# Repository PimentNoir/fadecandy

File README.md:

Fadecandy is a project that makes LED art easier, tastier, and more creative. We're all about creating tools that remove the technical drudgery from making LED art, freeing you to do more interesting, nuanced, and creative things. We think LEDs are more than just trendy display devices, we think of them as programmable light for interactive art.

* [Video Introduction to Fadecandy](https://vimeo.com/79935649)
* [Introduction by Nick Poole from Spark Fun Electronics](https://www.youtube.com/watch?v=-4AUBjV7Y-w)
* [Tutorial: LED Art with Fadecandy](https://learn.adafruit.com/led-art-with-fadecandy)
* [Tutorial: 1,500 NeoPixel LED Curtain with Raspberry Pi and Fadecandy](https://learn.adafruit.com/1500-neopixel-led-curtain-with-raspberry-pi-fadecandy/)
* [Presentation slides: Easier and Tastier LED Art with Fadecandy](http://www.misc.name/easier-and-tastier-led-art-with-fadecandy/)
* [LED Interaction Research with Fadecandy at Stimulant labs](http://stimulant.com/led-interaction-research/)

Buy a Fadecandy Controller board:

* [Adafruit](http://www.adafruit.com/products/1689)
* [RGB-123](http://rgb-123.com/product/fadecandy/)

Simple Example
--------------

Here's a simple project, a single LED strip controlled by a Processing sketch running on your laptop:

```
// Simple Processing sketch for controlling a 64-LED strip.
// A glowing color-blob appears on the strip under mouse control.

OPC opc;
PImage dot;

void setup()
{
  size(800, 200);

  // Load a sample image
  dot = loadImage("color-dot.png");

  // Connect to the local instance of fcserver
  opc = new OPC(this, "127.0.0.1", 7890);

  // Map one 64-LED strip to the center of the window
  opc.ledStrip(0, 64, width/2, height/2, width / 70.0, 0, false);
}

void draw()
{
  background(0);

  // Draw the image, centered at the mouse location
  float dotSize = width * 0.2;
  image(dot, mouseX - dotSize/2, mouseY - dotSize/2, dotSize, dotSize);
}
```

A More Complex Example
----------------------

Fadecandy is also useful for larger projects with many thousands of LEDs, and it's useful for art that runs on embedded computers like the Raspberry Pi:

Project Scope
-------------

This project is a collection of reusable pieces you can take or leave. The overall goal of making LED art easier, tastier, and more creative is a broad one. To keep this project manageable to start with, there are some rough limitations on what's supported:

* LED strips, grids, and other modules based on the WS2811 or WS2812 chip.
  * Common and inexpensive, available from [many suppliers](http://www.aliexpress.com/item/5M-WS2811-LED-digital-strip-60leds-m-with-60pcs-WS2811-built-in-tthe-5050-smd-rgb/635563383.html?tracelog=back_to_detail_a) for around $0.25 per pixel.
* Something with a USB host port that can run your art.
  * Laptops and Mac Minis work great
  * The Raspberry Pi is also a great platform for this, but it requires more technical skill
* Distances of no more than 60ft or so between your computer and your farthest LEDs
  * USB cables < 50ft
  * WS2811 data cables < 10ft
* No more than about 10000 LED pixels total
  * There's no hard limit, but it gets more difficult after this point.
* Experimental support for APA102/APA102C/SK9822 via SPI
  * Currently only works on Raspberry Pi and requires the WiringPi library. Compile with FCSERVER_HAS_WIRINGPI defined to enable support.

These are fuzzy limitations based on current software capabilities and rough electrical limits, so you may be able to stretch them. But this gives you an idea about the kind of art we try to support. Projects are generally larger than wearables, but smaller than entire buildings.

For example, the first project to use Fadecandy was the [Ardent Mobile Cloud Platform](http://scanlime.org/2013/09/the-ardent-mobile-cloud-platform/) at Burning Man 2013. This project used one Raspberry Pi, five Fadecandy controller boards, and 2500 LEDs.

Fadecandy makes no assumptions about how you generate control patterns for the LEDs. You can generate a 2D video and sample pixels from the video, you can make a 3D model of your sculpture and sample a 3D *shader* for your pixel values, or you can create a unique system specifically for your art.

Fadecandy Controller
--------------------

The centerpiece of the Fadecandy project is a controller board which can drive up to 512 LEDs (as 8 strings of 64) over USB. Many Fadecandy boards can be attached to the same computer using a USB hub or a chain of hubs.

Fadecandy makes it easy to drive these LEDs from anything with USB, and it includes unique algorithms which eliminate many of the common visual glitches you see when using these LEDs.

The LED drive engine is based on Stoffregen's excellent [OctoWS2811](http://www.pjrc.com/teensy/td_libs_OctoWS2811.html) library, which pumps out serial data for these LED strips entirely using DMA. This firmware builds on Paul's work by adding:

* A high performance USB protocol
* Zero copy architecture with triple-buffering
* Interpolation between keyframes
* Gamma and color correction with per-channel lookup tables
* Temporal dithering
* A custom PCB with line drivers and a 5V boost converter
* A fully open source bootloader

These features add up to give *very smooth* fades and high dynamic range. Ever notice that annoying stair-stepping effect when fading LEDs from off to dim? Fadecandy avoids that using a form of [delta-sigma modulation](http://en.wikipedia.org/wiki/Delta-sigma_modulation). It rapidly wiggles each pixel's value up or down by one 8-bit step, in order to achieve 16-bit resolution for fades.

Vitals
------

* 512 pixels supported per Teensy board (8 strings, 64 pixels per string)
* Very high hardware frame rate (~400 FPS) to support temporal dithering
* Full-speed (12 Mbps) USB
* 257x3-entry 16-bit color lookup table, for gamma correction and color balance

Platform
--------

Fadecandy uses the Freescale MK20DX128 microcontroller, the same one used by the [Teensy 3.0](http://www.pjrc.com/store/teensy3.html) board. Fadecandy includes its own PCB design featuring a robust power supply and level shifters. It also includes an open source bootloader compatible with the USB Device Firmware Update spec.

You can use Fadecandy either as a full hardware platform or as firmware for the Teensy 3.0 board.

Color Processing
----------------

Fadecandy internally represents colors with 16 bits of precision per channel, or 48 bits per pixel. Why 48-bit color? In combination with our dithering algorithm, this gives a lot more color resolution. It's especially helpful near the low end of the brightness range, where stair-stepping and color *popping* artifacts can be most apparent.

Each pixel goes through the following processing steps in Fadecandy:

* 8 bit per channel framebuffer values are expanded to 16 bits per channel
* We interpolate smoothly from the old framebuffer values to the new framebuffer values
* This interpolated 16-bit value goes through the color LUT, which itself is linearly interpolated
* The final 16-bit value is fed into our temporal dithering algorithm, which results in an 8-bit color
* These 8-bit colors are converted to the format needed by OctoWS2811's DMA engine
* In hardware, the converted colors are streamed out to eight LED strings in parallel

The color lookup tables can be used to implement gamma correction, brightness and contrast, and white point correction. Each channel (RGB) has a 257 entry table. Each entry is a 16-bit intensity. Entry 0 corresponds to the 16-bit color 0x0000, entry 1 corresponds to 0x0100, etc. The 257th entry corresponds to 0x10000, which is just past the end of the 16-bit intensity space.

Keyframe Interpolation
----------------------

By default, Fadecandy interprets each frame it receives as a keyframe. In-between these keyframes, Fadecandy will generate smooth intermediate frames using linear interpolation. The interpolation duration is determined by the elapsed time between when the final packet of one frame is received and when the final packet of the next frame is received.

This scheme works well when frames are arriving at a nearly constant rate. If frames suddenly arrive slower than they had been arriving, interpolation will proceed faster than it optimally should, and one keyframe will hold steady until the next keyframe arrives. If frames suddenly arrive faster than they had been arriving, Fadecandy will need to jump ahead in order to avoid falling behind.

This keyframe interpolation is not intended as a substitute for other forms of animation control. It is intended to generate high-framerate video from a source that operates at typical video framerates.

Open Pixel Control Server
-------------------------

The Fadecandy project includes an [Open Pixel Control](http://openpixelcontrol.org/) server which can drive multiple Fadecandy boards and DMX adaptors. USB devices may be hotplugged while the server is up, and the server uses a JSON configuration file to map OPC messages to individual Fadecandy boards and DMX devices.

Why use Open Pixel Control?

* You can keep your effects code portable among different lighting controllers.
* OPC includes an OpenGL-based simulator, allowing you to develop effects before the hardware is done.
* The OPC server manages USB hotplug and multi-device synchronization, so you don't have to.
* The OPC server loads color-correction data into each Fadecandy board.

WebSockets Server
-----------------

In addition to Open Pixel Control, `fcserver` also supports WebSockets, so you can write LED art algorithms and utilities in Javascript using the plethora of libraries and tools available on that platform. LED art can be easily integrated with any input device or library that will run in the browser or Node.

Browser UI
----------

When you run `fcserver`, it also gives you a simple browser-based UI for identifying the attached Fadecandy Controllers and quickly testing your lights. By default, this UI runs on [http://localhost:7890](http://localhost:7890).

Where to?
---------

* [Video introduction by Nick Poole from Spark Fun Electronics](https://www.youtube.com/watch?v=-4AUBjV7Y-w)
* Tutorial: ["LED Art with Fadecandy"](https://learn.adafruit.com/led-art-with-fadecandy)
* Sample projects are in [examples](https://github.com/scanlime/fadecandy/tree/master/examples)
* Pre-compiled binaries are in [bin](https://github.com/scanlime/fadecandy/tree/master/bin)
* More documentation is included in [doc](https://github.com/scanlime/fadecandy/tree/master/doc)
  * [Open Pixel Control Protocol](https://github.com/scanlime/fadecandy/blob/master/doc/fc_protocol_opc.md)
  * [WebSocket Protocol](https://github.com/scanlime/fadecandy/blob/master/doc/fc_protocol_websocket.md)
  * [USB Protocol](https://github.com/scanlime/fadecandy/blob/master/doc/fc_protocol_usb.md)
  * [Processing OPC Client](https://github.com/scanlime/fadecandy/blob/master/doc/processing_opc_client.md)
  * [Server Configuration](https://github.com/scanlime/fadecandy/blob/master/doc/fc_server_config.md)
  * ...or if you still have questions, ask the [discussion group](https://groups.google.com/forum/#!forum/fadecandy)
* Buy a Fadecandy Controller board
  * [Adafruit](http://www.adafruit.com/products/1689)
  * [RGB-123](http://rgb-123.com/product/fadecandy/)

Frequently Asked Questions
--------------------------

### Why can't you use more than 64 LEDs per strip?

This limit comes from the data rate of the WS2811 LED controller's protocol (800 kbps) and the frame rate that seems to be needed to get the best results from our temporal dithering algorithm (about 400 FPS).

With the WS2811 protocol, each bit takes 1.25 microseconds to transmit, and there's a 50 microsecond reset state that happens once per frame. Each LED has 24 bits of data. We can use this to relate number of LEDs to frames per second:

```
(a)   fps = 1 / ( 0.00000125 * 24 * numLEDs + 0.00005 )
(b)   numLEDs = floor( (1 / fps - 0.00005) / 0.00000125 / 24 )
```

Equation (a) tells us that the theoretical maximum frame rate for 64 LEDs is 507.6 FPS. The Fadecandy Controller actually gets more like 425 FPS most of the time, since the CPU speed tends to be the limiting factor. With Equation (b), we can see that a theoretical strip length of 81 would still let us get 403 FPS. So why did I choose 64 instead of 81? Powers of two, mostly, and I honestly chose the limit of 64 before I knew exactly what frame rates would be necessary.

It would be possible to drive LED strips of around 80 LEDs in length with the same quality using a slightly more powerful microcontroller, as long as we don't rely on the strip length to be a power of two.

### Will Fadecandy work on the Teensy 3.1 board?

Currently, no. The Teensy 3.1 uses a different microcontroller with a slightly different memory layout which would make it impractical to have one firmware image that's binary-compatible with both the Teensy 3.1 and the Teensy 3.0 / Fadecandy Controller board. This is a thing that's certainly doable, but I haven't wanted to spend the extra maintenance effort to maintain and test a binary image for a second architecture.

If anyone reading is passionate about supporting the Teensy 3.1 and would volunteer to maintain a port, I'd be happy to point you toward the modifications that would be necessary.

### Would Fadecandy be able to take advantage of the additional processing power on the Teensy 3.1's microcontroller?

A little bit, maybe! But it wouldn't be a dramatic improvement, if we wanted to keep the exact same quality of dithering.

With some extra processing power and RAM, the strip length limit could be increased from 64 to around 80. This is hardly a dramatic increase, though. The intrinsic limits explained above are more of a factor in the design than the CPU or RAM limits.

### Can you use multiple Fadecandy controllers at once?

Yes! You can use USB hubs to connect many Fadecandy boards to one controller.

### What are the limits? How big can Fadecandy go?

Fadecandy limits include USB bus bandwidth, Open Pixel Control packet size, and CPU power. 

USB Bus bandwidth will start to be a problem around a dozen Fadecandy boards per USB host controller. This may start to depend on the details of the computer you're using. On a laptop, each USB port will usually have an independent allocation of bandwidth available. So, connect the first dozen Fadecandy boards to one USB port, then the second dozen to another USB port, etc. If you do connect more than the recommended number of Fadecandy controllers to one port they'll still work, but frame rate will start to decrease.

The [Open Pixel Control](http://openpixelcontrol.org/) protocol used by Fadecandy has a packet size limit of 64 kilobytes, or 21845 LEDs. Any more than that will require workarounds, such as extending the OPC protocol or using multiple OPC channels.

And then there's CPU power... these limits will depend on the language and framework your code uses, and what kind of computer you're running from. A large installation with 10,000 LEDs will probably need to run off of a laptop or Mac Mini unless your code is quite efficient. Smaller installations with up to 1000 LEDs or so could run off of something as small as a Raspberry Pi. But these are very broad generalizations, and this all depends on how much processing you need to perform per-LED. Keep in mind the scalability levels of your particular framework when you plan to build a large installation.

### The Raspberry Pi is kind of slow. What other small embedded Linux computers are available?

There are a lot of options to choose from, but my current favorite is the [ODROID-U3](http://www.hardkernel.com/main/products/prdt_info.php?g_code=G138745696275). It's about the same size as a Raspberry Pi, with a 1.7 GHz quad-core ARM. There's an optional fan add-on, but I haven't found it to be necessary yet.

### I'm using Windows 7, and the driver for Fadecandy doesn't load. What can I do?

Make sure you have all available Windows updates installed. Fadecandy uses a Windows feature ([WCID](https://github.com/pbatard/libwdi/wiki/WCID-Devices)) that wasn't present in the original retail version of Windows 7, but it was added in a subsequent update.

For reference, this is a 
[series of screenshots](http://imgur.com/a/0MAFR) showing a Fadecandy controller attached to a freshly installed Windows 7 Home Professional 32-bit virtual machine. At first it fails (no driver for "Fadecandy") but after updating Windows, it finds the correct device (WinUSB) and fcserver connects to it.

If that doesn't fix it, you may have a version of Windows with an inexplicably broken `WinUSB` driver. The French version of Windows 7 SP1 seems to be afflicted by this bug, and possibly others. As a workaround, you can use the [Zadig](http://zadig.akeo.ie/) utility to manually install an alternative driver. Use the arrows to change the driver on the right side of the arrow from `WinUSB` to `libusbK`, then click "Install Driver". You can see a [series of screenshots](http://imgur.com/a/25V81) illustrating this.

If you're still having trouble, please ask for help on the [discussion group](https://groups.google.com/forum/#!forum/fadecandy) or [bug tracker](https://github.com/scanlime/fadecandy/issues) and we can get to the bottom of this problem together. Thanks for your patience!

Contact
-------

Please direct questions to the [Discussion group](https://groups.google.com/forum/#!forum/fadecandy), it's full of smart and creative people who can help!

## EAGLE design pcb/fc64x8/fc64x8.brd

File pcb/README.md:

Fadecandy Controller Boards
===========================

This directory contains information and design files for the various circuit boards that you can run Fadecandy firmware on.

Teensy 3.0
----------

The [Teensy 3.0](http://www.pjrc.com/teensy/) microcontroller board from PJRC was the original development platform for Fadecandy. You can still run the Fadecandy firmware, including the bootloader, on this platform.

* Use the [Teensy Loader](http://www.pjrc.com/teensy/loader.html) to install a [Firmware Binary](https://raw.github.com/scanlime/fadecandy/master/bin/fc-firmware-v106.hex) on your Teensy 3.0
* Bridge pins 15 and 16
* Wire your LEDs according to the diagram:

**Warning:** The Teensy's output signals are 3.3V, whereas the WS2811 LEDs expect a 5V signal. It will often work anyway, but this tends to be unreliable if your LED power supply voltage isn't consistent or if your wires aren't very short.

Fc64x8 Revision A
-----------------
 
This board uses the same microcontroller as the Teensy 3.0 board, a Freescale Kinetis K20. There are several differences from the Teensy 3.0, however, that make it easier to use and more reliable for LED applications:

* It comes pre-programmed with the Fadecandy firmware.
* The Fadecandy board has a more convenient pinout, with more ground pads and with the LED strings organized sensibly.
* The Teensy uses 3.3v IO which doesn't work reliably with the WS2811 LEDs. Fadecandy includes a level shifter and series termination resistors.
* Fadecandy also includes a boost converter power supply to generate a stable 5V for the level shifter even when the USB power is noisy or sagging due to long cables.
* The Teensy uses a proprietary bootloader implemented on a separate microcontroller. The Fadecandy board has an open source bootloader that runs on the same microcontroller as the firmware, and it speaks the standard DFU protocol.

The PCB design for this revision is tagged as **fc64x8-rev-a** in Git. This board was manufactured in a limited run of 100, and availability has been very limited.

* [PCB Design Files](https://github.com/scanlime/fadecandy/tree/fc64x8-rev-a/pcb/fc64x8)
* Design software is [Eagle CAD](http://www.cadsoftusa.com/)

Fc64x8 Revision B
-----------------

Electrically the same as Revision A, this is the version produced by Adafruit. It is slightly larger, at 0.8" by 1.25". It uses a mini-USB instead of a micro-USB connector, and includes two extra small holes at the top corners for mounting onto larger boards.

RGB-123 Fadecandy Controller
----------------------------

This is a new board layout for Fadecandy which uses different component packages. It is produced and sold by Ryan O'Hara at RGB-123. The current version is Revision G.

Test Jig
--------

This board, with the help of a Teensy 3.0 and the testjig firmware, performs automated factory tests and firmware installation on Fadecandy boards.

The design was contributed by Ryan O'Hara of RGB-123.

* [Order PCBs via OSH Park](http://oshpark.com/shared_projects/0Hx8kSYR)
* Design software is [LabCenter Proteus](http://www.labcenter.co.uk/)

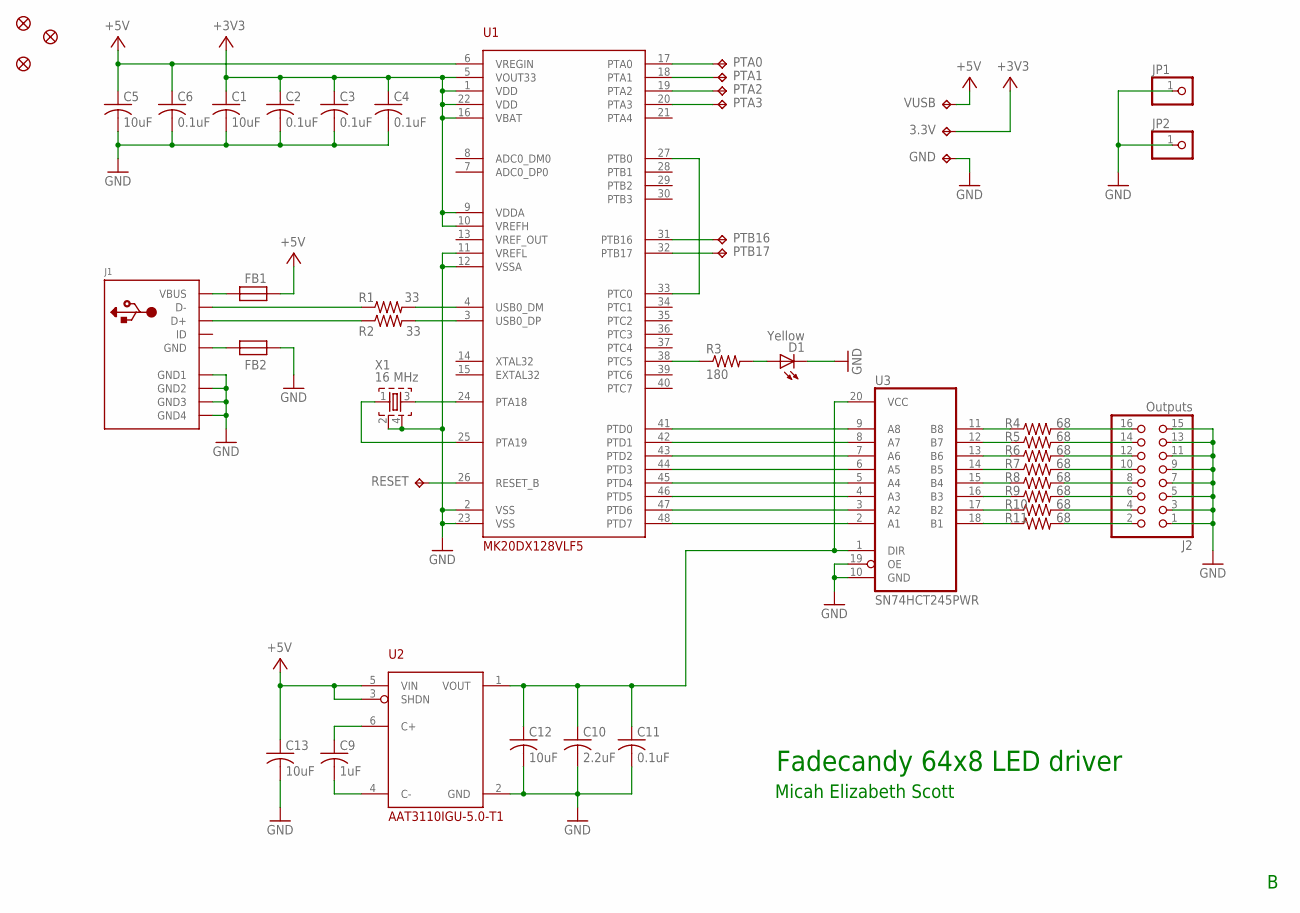
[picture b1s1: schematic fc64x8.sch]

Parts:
3.3V: TPTP18SQ; TP18SQ
C1, C5, C12, C13: 10uF; 0805
C2, C3, C4, C6, C11: 0.1uF; 0805
C9: 1uF; 0805
C10: 2.2uF; 0805
D1: Yellow; CHIP-LED0805
FB1, FB2: FB0805/NO-OUTLINE; 0805
FID1, FID2, FID3: FIDUCIAL""; FIDUCIAL_1MM
GND: TPTP18SQ; TP18SQ
J1: USBMINIB; USB-MINIB
J2: Outputs; 2X08
JP1, JP2: PINHD-1X1; 1X01
PTA0, PTA1, PTA2, PTA3: TPTP18SQ; TP18SQ
PTB16, PTB17: TPTP18SQ; TP18SQ
R1, R2: 33; 0805
R3: 180; 0805
R4, R5, R6, R7, R8, R9, R10, R11: 68; 0805
RESET: TPTP18SQ; TP18SQ
U1: MK20DX128VLF5; LQFP48
U2: AAT3110IGU-5.0-T1; SOT23-6L
U3: SN74HCT245PWR; TSSOP20
VUSB: TPTP18SQ; TP18SQ
X1: 16 MHz; TSX-3225

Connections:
+3V3: 3.3V.TP, C1.1, C2.1, C3.1, C4.1, U1.1 (VDD), U1.5 (VOUT33), U1.9 (VDDA), U1.10 (VREFH), U1.16 (VBAT), U1.22 (VDD)
+5V: C5.1, C6.1, C13.1, FB1.2, U1.6 (VREGIN), U2.3 (SHDN), U2.5 (VIN), VUSB.TP
GND: C1.2, C2.2, C3.2, C4.2, C5.2, C6.2, C10.2, C11.2, C12.2, C13.2, D1.C, FB2.2, GND.TP, J1.GND1, J1.GND2, J1.GND3, J1.GND4, J2.1, J2.3, J2.5, J2.7, J2.9, J2.11, J2.13, J2.15, JP1.1, JP2.1, U1.2 (VSS), U1.11 (VREFL), U1.12 (VSSA), U1.23 (VSS), U2.2 (GND), U3.10 (GND), U3.19 (OE), X1.2, X1.4
unnamed: R3.1, U1.38 (PTC5)
unnamed: U1.24 (PTA18), X1.3
unnamed: D1.A, R3.2
unnamed: U1.25 (PTA19), X1.1
unnamed: FB1.1, J1.VBUS
unnamed: U1.27 (PTB0), U1.33 (PTC0)
unnamed: FB2.1, J1.GND
unnamed: U1.41 (PTD0), U3.9 (A8)
unnamed: J1.D-, R1.1
unnamed: J1.D+, R2.1
unnamed: R1.2, U1.4 (USB0_DM)
unnamed: R2.2, U1.3 (USB0_DP)
unnamed: U1.42 (PTD1), U3.8 (A7)
unnamed: U1.43 (PTD2), U3.7 (A6)
unnamed: U1.44 (PTD3), U3.6 (A5)
unnamed: U1.45 (PTD4), U3.5 (A4)
unnamed: U1.46 (PTD5), U3.4 (A3)
unnamed: U1.47 (PTD6), U3.3 (A2)
unnamed: U1.48 (PTD7), U3.2 (A1)
unnamed: R4.1, U3.11 (B8)
unnamed: C9.1, U2.6 (C+)
unnamed: C9.2, U2.4 (C-)
unnamed: R5.1, U3.12 (B7)
unnamed: R6.1, U3.13 (B6)
unnamed: R7.1, U3.14 (B5)
unnamed: R8.1, U3.15 (B4)
unnamed: C10.1, C11.1, C12.1, U2.1 (VOUT), U3.1 (DIR), U3.20 (VCC)
unnamed: R9.1, U3.16 (B3)
unnamed: R10.1, U3.17 (B2)
unnamed: R11.1, U3.18 (B1)
unnamed: J2.16, R4.2
unnamed: J2.14, R5.2
unnamed: J2.12, R6.2
unnamed: J2.10, R7.2
unnamed: J2.8, R8.2
unnamed: J2.6, R9.2
unnamed: J2.4, R10.2
unnamed: J2.2, R11.2
unnamed: RESET.TP, U1.26 (RESET_B)
unnamed: PTA0.TP, U1.17 (PTA0)
unnamed: PTA1.TP, U1.18 (PTA1)
unnamed: PTA2.TP, U1.19 (PTA2)
unnamed: PTA3.TP, U1.20 (PTA3)
unnamed: PTB16.TP, U1.31 (PTB16)
unnamed: PTB17.TP, U1.32 (PTB17)

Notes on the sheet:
Fadecandy 64x8 LED driver
Micah Elizabeth Scott

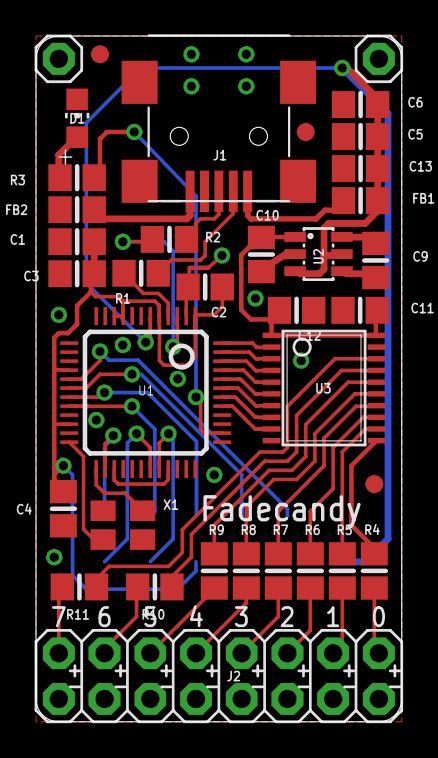
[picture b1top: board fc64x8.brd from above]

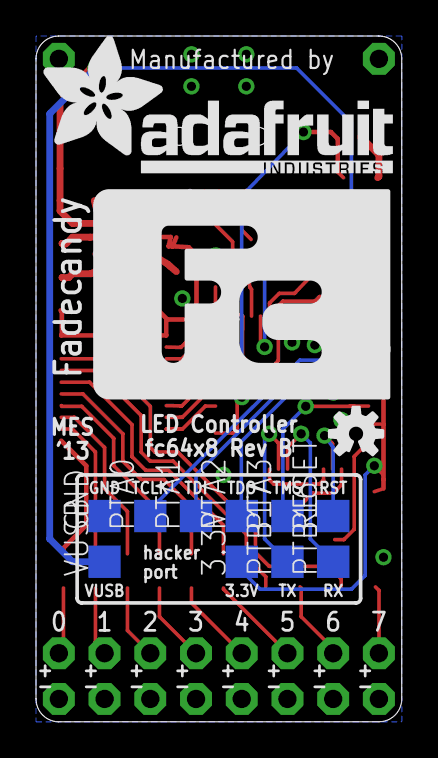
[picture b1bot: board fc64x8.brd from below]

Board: 2 copper layers, 20.3 x 38.1 mm, 48 parts (12 on the bottom side), 48 nets.

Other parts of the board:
U$1: OSHW-LOGO-S
U$2: ADAFRUIT_TEXT_20MM

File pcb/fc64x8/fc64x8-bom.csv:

Qty,Refs,Mfg. Part,Description,Package,Supplier,Supplier Part,$ single,$ qty 100,URL,Extended $ single,Extended $ qty 100,,
1,U1,MK20DX128VLF50,ARM Cortex-M4 microcontroller,LQFP-48,Digi-Key,MK20DX128VLF50-ND,$4.78,$2.66,http://www.digikey.com/product-detail/en/MK20DX128VLF5/MK20D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,$4.78,$2.6568,Total qty 1:,$8.78
1,X1,TSX-3225 16.0000MF18X-AC3,16 MHz crystal,custom,Digi-Key,SER3636CT-ND,$0.63,$0.42,http://www.digikey.com/product-detail/en/TSX-3225%2016.0000M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,$0.63,$0.42,Total qty 100:,$4.64142
5,"C2,3,4,6,11",CL10F104ZA8NNNC,0.1uF ceramic cap,SMT 0603,Digi-Key,1276-1011-1-ND,$0.10,$0.01,http://www.digikey.com/product-detail/en/CL10F104ZA8NNNC/127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,$0.5,$0.038,Retail estimate:,$13.92426
3,"C1,5,10",CC0603ZRY5V5BB225,2.2uF ceramic cap,SMT 0603,Digi-Key,311-1452-1-ND,$0.11,$0.04,http://www.digikey.com/product-detail/en/CC0603ZRY5V5BB225/3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,$0.33,$0.108,,
1,U2,AAT3110IGU-5.0-T1,5V switched cap boost converter,SOT23-6,Digi-Key,863-1505-1-ND,$0.30,$0.26,http://www.digikey.com/product-detail/en/AAT3110IGU-5.0-T1/8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,$0.3,$0.26,,
1,J1,10118194-0001LF,"Micro USB, SMT, 4 DIP legs",custom,Digi-Key,609-4618-1-ND,$0.46,$0.30,http://www.digikey.com/product-detail/en/10118194-0001LF/609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,$0.46,$0.3032,,
2,"FB1,2",ACML-0603-060-T,"Ferrite bead, 1A",SMT 0603,Digi-Key,ACML-0603-060-TCT-ND,$0.05,$0.03,http://www.digikey.com/product-detail/en/ACML-0603-060-T/ACM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,$0.1,$0.066,,
2,"R1,2",RMCF0603JT33R0,"33 ohm resistor, 1/10 W 5%",SMT 0603,Digi-Key,RMCF0603JT33R0CT-ND,$0.02,$0.01,http://www.digikey.com/product-detail/en/RMCF0603JT33R0/RMCF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,$0.04,$0.014,,
1,U3,SN74HCT245PWR,Octal buffer,TSSOP-20,Digi-Key,296-8404-1-ND,$0.51,$0.32,http://www.digikey.com/product-detail/en/SN74HCT245PWR/296-8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,$0.51,$0.3245,,
1,R3,RMCF0603JT180R,"180 ohm resistor, 1/10 W 5%",SMT 0603,Digi-Key,RMCF0603JT180RCT-ND,$0.02,$0.01,http://www.digikey.com/product-detail/en/RMCF0603JT180R/RMCF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,$0.02,$0.007,,
1,D1,LY Q976-P1S2-36,Yellow LED,SMT 0603,Digi-Key,475-2558-1-ND,$0.09,$0.06,http://www.digikey.com/product-detail/en/LY%20Q976-P1S2-36/4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,$0.09,$0.0575,,
2,"C7,8",T491A106K010AT,"10uF tantalum cap, 10V",SMT 1206,Digi-Key,399-3684-1-ND,$0.38,$0.17,http://www.digikey.com/product-detail/en/T491A106K010AT/399-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,$0.76,$0.3368,,
1,C9,CC0603ZRY5V6BB105,1uF ceramic cap,SMT 0603,Digi-Key,311-1357-1-ND,$0.10,$0.02,http://www.digikey.com/product-detail/en/CC0603ZRY5V6BB105/3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,$0.1,$0.0189,,
8,R4-11,RMCF0603JT75R0,"75 ohm resistor, 1/10 W 5%",SMT 0603,Digi-Key,RMCF0603JT75R0CT-ND,$0.02,$0.00,http://www.digikey.com/product-detail/en/RMCF0603JT75R0/RMCF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,$0.16,$0.03072,,
1,J2-1,68602-116HLF,"Header 8x2 0.1"" gold plated","0.1"" 8x2 TH",Digi-Key,609-3364-ND,$0.46,$0.34,http://www.digikey.com/product-detail/en/68602-116HLF/609-33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,,,,
1,J2-2,101-166,"IDC socket 8x2 0.1""",IDC,Digi-Key,ED10502-ND,$0.33,$0.22,http://www.digikey.com/product-detail/en/101-166/ED10502-ND/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,,,,

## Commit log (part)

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2014-02-11 Fix submodule target path in the server Makefile.
2014-02-13 Adjust parameters for better pacing
2014-02-13 Add a really simple burn-in test helper
2014-02-15 Some light improvements to the video processing examples.
2014-02-15 Fixlet to 11x11 grid test.
2014-02-15 More keys for movie speed control.
2014-02-15 Intermediate work on long strip (256 leds) support.
2014-02-15 Cleanup in the video grid 8x8 example.
2014-02-15 Use files list variable in the clean target.
    TODO: Maybe add CLEAN_FILES variable to handle the files list in
    the clean target.
2014-02-15 Port the rings_lamp processing scenario to 8x8 grid.
2014-02-15 Permit to set movie speed in processing one video example.
2014-02-15 Processing video test example for 16x16 grid.
    It's part of a much more complex project to support long strip.
2014-02-15 Minor improvement to the particule example for 8x8 grid.
2014-02-15 Remove a file commited by mistake.
2014-02-15 Small tests on examples for processing: * Use a remote fadecandy server; * Reapply blur and test filter on video processing.
2014-02-16 Tasty FFT spiral demo for the 32x16 panel
    Music not included this time, sadly.
2014-02-16 First pass at smoothing the particles movement in processing example.
2014-02-17 Improvements to processing FFT example for grid 8x8: - No need for a FFT array; - Differenciate player functionnality from line in capture. - Debug on for minim library.
    And some code cleanups.
2014-02-17 Polish a bit the FFT processing example for grid8x8.
    Add a some TODO comments.
2014-02-19 Update fc64x8 CAD files with final design from Adafruit
    - Remove outdated BOM file (Adafruit doesn't use a separate BOM spreadsheet)
    - Added fiducials
    - Added Adafruit logo
2014-02-20 Python 3 compatibility
2014-02-23 Implement an FBM for simplex noise + code cleanups.
2014-02-23 Variant of grid32x16z_particle_fft using line input
2014-02-24 Code cleanup on the FFT processing example for grid8x8 and tuning on the noise dimension seeding.
2014-02-24 New diagrams
    Details of how fcserver and the controller operate
2014-02-25 Mention CAD packages in README
2014-02-26 Add a triangle FFT visualizer tweaked for mic input
2014-02-26 New particle system example in Node.js
2014-02-26 Gracefully handle unmapped LEDs in opc.js
2014-02-26 Code cleanup on grid8x8 FFT processing example.
2014-02-27 Node.js version of the "rings" effect
2014-02-28 Parameter tweaks at the CODAME booth
2014-03-03 Particle system example with TouchOSC control
2014-03-07 Make http manifest.py work with python3+ as well as 2.7
2014-03-07 Different kind of left-hand wobble, closer to what we wanted
2014-03-07 Fix spin rate (pitch bend) control
2014-03-07 experiment: origin circulates
2014-03-08 Timestep cleanup
    Also allows particle lifetime to be dynamic again.
2014-03-08 Command line args
2014-03-09 Add a simple effect framework for C++
2014-03-09 Simplify C++ library, put everything in the headers
2014-03-09 Fix random walk on W axis, decrease hue variation
2014-03-09 Add sq() utility
2014-03-09 First cut at a port of Rings to c++
2014-03-09 SVL: Use 32-bit float by default
2014-03-09 FrameInfo object
    This gives effects global information about the frame, before and after rendering pixels. This
    can make some effects more convenient to write, and it allows effects to keep track of global per-pixel
    data if they need to.
2014-03-10 More ignorables for C++ examples
2014-03-10 Extensible argument parsing
2014-03-10 Prevent currentScale from reaching zero
    This would cause the algorithm to get stuck forever
2014-03-10 Header file path cleanup
    Now you can include these without changing the header path at all
2014-03-10 Add C++ examples to README
2014-03-10 Use a different name for integer-coordinate samplers
    It was too easy to accidentally use the integer version before. Now it's convenient to sample from floats or a Vec2.
2014-03-10 Particle system example for C++
2014-03-11 Build fixes for C++ examples on Linux
2014-03-11 Consistency fixes for ParticleEffect
2014-03-11 Remove broken dynamic blocksize from pooled allocator
    This was causing a compiler warning
2014-03-11 Set framerate to 72 fps. Entertainement people say it's emotionaly better.
2014-03-12 README for C++ library
2014-03-12 Unify 2D and 3D versions of "rings", add finer-grained early exit
2014-03-12 Move interesting effects into reusable headers
2014-03-12 Fix brightness scaling in Rings when rendering pauses
2014-03-12 EffectMixer example
2014-03-12 Cleanup: Split effect.h, rename opc_client
2014-03-12 Don't disable exceptions, nanoflann needs them
2014-03-13 Mention multi-core rendering in the README
2014-03-13 Missing postProcess() in Brightness adaptor
2014-03-13 Const accessors for Header
2014-03-14 Fine tune the brightness on the processing particles example for grid 8x8.
2014-03-15 Fine tune the processing example for grid8x8 with FFT.
    * Size bug;
    * Out of screen particles;
    * Brightness on the HSB color gradient generator.
2014-03-17 Rename random-color-pixel-strip to random-color-pixel-strip.html
2014-03-17 Fix Spacing
    Fix line spacing
2014-03-22 Code cleanup and better default values.
2014-03-26 Processing examples: grid8x8 FFT particules.
    Give default values a very smooth visual rendering and fix
    a couple of harmless bugs.
2014-03-30 New EffectMixer methods clear() and set()
2014-03-30 Command line option to scale speed
    Helps with testing effects in fast/slow motion
2014-04-04 Processing examples: grid8x8 FFT improvements.
    * Simulate a linear chirp pulse on FFT frequencies.
    * Implement 1D simplexnoise.
    * Code cleanups.
2014-04-04 Better comments on processing grid8x8 FFT example.
2014-04-04 More comments fixlets in the grid8x8 FFT processing example.
2014-04-04 Adjust the default particules minSize in the FFT processing example for grid8x8.
2014-04-05 grid8x8 FFT processing example:
    Improve a bit the debug ouput of the audio player.
2014-04-15 grid8x8 FFT processing example: simplify the logic that permit to choose between FFT filter type.
2014-04-15 Document the pin out number on teensy 3.X.
2014-04-15 Linker portage form latest teensy firmware.
2014-04-15 processing examples: partially revert an ugly hack.
2014-04-15 Allow for real to play with the chirp phase in the grid8x8 FFT example.
2014-04-15 More work on the teensy 3.1 firmware portage. Signed-off-by: Piment Noir Task Force <elecdev@piment-noir.org>
2014-04-15 Grid8x8 processing example: allow to play with the pulse phase everywhere. Signed-off-by: Piment Noir Task Force <elecdev@piment-noir.org>
2014-04-15 Add a file to git for teensy 3.1 portage work.
2014-04-15 Fix the log chirp in the grid8x8 processing example.
2014-04-15 Implement properly 4 chirp pulses in the grid8x8 FFT processing example.
2014-04-15 Grid8x8 FFT processing example: reduce global variables to the bare minimum to ease factorization. Signed-off-by: Piment Noir Task Force <elecdev@piment-noir.org>
2014-04-15 Processing examples: Code cleanup in all videos example and bug fix on the zoom.
2014-04-17 Random build fixes for Linux
2014-04-17 Many more particle sampling functions, including intensity gradient
2014-05-05 fcserver-osx v1.03
2014-05-05 fcserver.exe v1.03
2014-05-05 KD-Tree index for FrameInfo
2014-05-05 Note that the CPP examples are Mac/Linux only for now
2014-05-09 Adding perl OPC module and examples
2014-05-10 Windows fcserver-1.04
2014-05-10 Fix template syntax that old GCC versions dislike
2014-05-10 Example config file that just swaps red and blue
2014-05-25 Add ledRing() to OPC.pde
2014-06-02 Changes for midi_particles in the Un Sospiro video
    - Remove MIDI inputs that only make sense on the Q49 keyboard
    - Expire particles with zero intensity, and cap the max particles
    - Lower particle generation rate
2014-06-10 Processing grid8x8 FFT example:
    Small code cleanup.
2014-06-11 Processing grid8x8 FFT example:
    Add TODO list.
2014-06-20 Further Experiment with Mitch on Grid8x8 FFT
2014-06-22 grid8x8 FFT example: small code cleanups
2014-07-04 Amend copyright in grid8x8 FFT example.
2014-07-09 better living through list comprehension: performance tweak on opc.py
2014-07-10 Processing example grid8x8 FTT : Fix a typo
2014-07-24 Add a FAQ, update some of the documentation links
2014-08-03 Update opc.py
    struct import missing
2014-08-13 Grid8x8 FFT example: Refine usage rights.
2014-08-24 Recommend libusbK and Zadig in the FAQ
2014-08-24 remove old test
2014-09-04 Implement properly the four dimensions FBM around the simplex noise make use of the 2D one.
2014-09-13 Rename NetServer to TcpNetServer, making room for a separate one for UDP
2014-09-28 Processing: OPC (re)connection in separate thread
    When using multiple OPC connections, prevents disconnected server(s)
    from stalling the client.
2014-10-08 Code cleanup for LFO demonstration.
2014-11-10 Grid8x8 FFT processing example: Make use of multithreaded OPC client.
    Courtesy of Micah and PaintYourDragon.
2014-12-27 Link to Stimulant's blog post from this summer
2015-02-19 Link to ODROID was causing chrome to download a .php file instead of opening a webpage
2015-04-12 Added java examples
2015-05-24 Makefile modifications to cross-compile for OpenWRT on OSX tested on OSX only, needs testing on Windows and Linux
2015-09-17 Creating colors with all blue components possible
2015-10-11 add connection error handling and reconnect
2015-11-30 Adjust the vertical
2015-12-23 Fix botched find / replace.
2016-01-03 Add explicit casts for TweakMode compatibility.
2016-04-16 Update OPC.pde to the lastest fixed version in all my personals works with processing.
    Postpone the update to the grid11x11 processing example,
    it depend on a firmware that support more leds and need a proper merging.
2016-07-01 Adds clarity to pointing to new config
    Offering details on how to use a new config file
2016-07-26 Give processing grid32x16z_particle_fft example a sensible sound file by default. ²
2016-08-03 Grid8x8 particles FFT processing example : - Code cleanup: remove dead code; formatting; - Fix access to static methods and variables.
2016-08-11 grid8x8_particle_fft: Maths cleanup.
2016-08-17 grid8x8_particle_fft: Do not compute internals averages on the FFT.
2016-08-25 grid8x8_particle_fft: First pass on a more standard key bindings.
    More to come ...
2016-08-31 grid8x8_particle_fft: Make debug class methods static.
2016-09-06 grid8x8_particle_fft: Add a comment for keybindings.
2016-09-06 grid8x8_particle_fft: Small cleanups and typos fixes.
2016-11-13 Added CSharp .NET Core examples
2016-11-15 updated colorutils due to overflow issue
2017-07-22 CMake, Systemd, debian package support
    CMake support was added as an alternative to the pure Makefile that already exists. CMake supports generating build files for a large set of different platforms. Makefiles, XCode project, Visual Stud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
    The CMake project includes build rules for installing, including running the server as a daemon using SystemD.
    Adding similar support for init would be possible as well.
    CMake is similar to configure + autoconf, so it is possible to turn on and off different features before compiling.
    The main reason for this change was to create an easily reproducible way to install the Fadecandy server as a daemon.
    The target for these efforts was mainl
2017-08-09 Fix CMAKE instructions
    Submodules must be present prior to running cmake.
2017-12-08 Adds message relaying over a second socket
2018-01-21 Removed unnessecary include and moved comment
2018-01-22 Add FCSERVER_HAS_WIRINGPI guards in fcserver.cpp
2018-03-27 Remove tabs introduced in scanlime/fadecandy@8934a74
2018-12-26 Tidying up examples/html/random-color-pixel-strip.html
2019-01-03 Added reference to new systemd examples

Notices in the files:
parts and their libraries:
SparkFun-Aesthetics: Licensing: CC v3.0 Share-Alike You are welcome to use this library for commercial purposes.
microbuilder: This work is placed in the public domain, and may be freely used for commercial and non-commercial work with the following conditions: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
